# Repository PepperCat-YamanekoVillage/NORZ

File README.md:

# NORZ

NORZ is a project to create a Z80-compatible CPU using only NOR gates.

</br>

The project is progressing according to the following roadmap:
- [x] Draft the CPU design based on the Z80 specifications
- [x] Write the Verilog code
- [x] Debug the Verilog code
- [x] Implement the design on boards
- [x] Make a test board
- [x] Test the test board
- [ ] Debug the boards

</br>

### My blogs (ja)

[Gates consisting of NOR](https://yamanekovillage.com/articles/norz_1/)

[Modules consisting of NOR](https://yamanekovillage.com/articles/norz_2/)

[NORZ(Z80)\'s architecture](https://yamanekovillage.com/articles/norz_3/)

[NORZ on Verilog](https://yamanekovillage.com/articles/norz_4/)

[Debuging Verilog codes](https://yamanekovillage.com/articles/norz_5/)

[Design PCBs](https://yamanekovillage.com/articles/norz_6/)

[Make a test board (Failed)](https://yamanekovillage.com/articles/norz_7/)

</br>

## Confirmed instructions in Verilog

### 8-Bit Load Group
- [x] LD r,r’
- [x] LD r,n
- [x] LD r,(HL)
- [x] LD r,(IX+d)
- [x] LD r,(IY+d)
- [x] LD (HL),r
- [x] LD (IX+d),r
- [x] LD (IY+d),r
- [x] LD (HL),n
- [x] LD (IX+d),n
- [x] LD (IY+d),n
- [x] LD A,(BC)
- [x] LD A,(DE)
- [x] LD A,(nn)
- [x] LD (BC),A
- [x] LD (DE),A
- [x] LD (nn),A
- [x] LD A,I
- [x] LD A,R
- [x] LD I,A
- [x] LD R,A

### 16-Bit Load Group
- [x] LD dd,nn
- [x] LD IX,nn
- [x] LD IY,nn
- [x] LD HL,(nn)
- [x] LD dd,(nn)
- [x] LD IX,(nn)
- [x] LD IY,(nn)
- [x] LD (nn),HL
- [x] LD (nn),dd
- [x] LD (nn),IX
- [x] LD (nn),IY
- [x] LD SP,HL
- [x] LD SP,IX
- [x] LD SP,IY
- [x] PUSH qq
- [x] PUSH IX
- [x] PUSH IY
- [x] POP qq
- [x] POP IX
- [x] POP IY

### Exchange, Block Transfer, and Search Group
- [x] EX DE,HL
- [x] EX AF,AF
- [x] EXX
- [x] EX (SP),HL
- [x] EX (SP),IX
- [x] EX (SP),IY
- [x] LDI
- [x] LDIR
- [x] LDD
- [x] LDDR
- [x] CPI
- [x] CPIR
- [x] CPD
- [x] CPDR

### 8-Bit Arithmetic Group
- [x] ADD A,r
- [x] ADD A,n
- [x] ADD A,(HL)
- [x] ADD A,(IX+d)
- [x] ADD A,(IY+d)
- [x] ADC A,r
- [x] ADC A,n
- [x] ADC A,(HL)
- [x] ADC A,(IX+d)
- [x] ADC A,(IY+d)
- [x] SUB r
- [x] SUB n
- [x] SUB (HL)
- [x] SUB (IX+d)
- [x] SUB (IY+d)
- [x] SBC r
- [x] SBC n
- [x] SBC (HL)
- [x] SBC (IX+d)
- [x] SBC (IY+d)
- [x] AND r
- [x] AND n
- [x] AND (HL)
- [x] AND (IX+d)
- [x] AND (IY+d)
- [x] OR r
- [x] OR n
- [x] OR (HL)
- [x] OR (IX+d)
- [x] OR (IY+d)
- [x] XOR r
- [x] XOR n
- [x] XOR (HL)
- [x] XOR (IX+d)
- [x] XOR (IY+d)
- [x] CP r
- [x] CP n
- [x] CP (HL)
- [x] CP (IX+d)
- [x] CP (IY+d)
- [x] INC r
- [x] INC (HL)
- [x] INC (IX+d)
- [x] INC (IY+d)
- [x] DEC r
- [x] DEC (HL)
- [x] DEC (IX+d)
- [x] DEC (IY+d)

### General-Purpose Arithmetic and CPU Control Groups
- [x] DAA
- [x] CPL
- [x] NEG
- [x] CCF
- [x] SCF
- [x] NOP
- [x] HALT
- [x] DI
- [x] EI
- [x] IM 0
- [x] IM 1
- [x] IM 2

### 16-Bit Arithmetic Group
- [x] ADD HL,ss
- [x] ADC HL,ss
- [x] SBC HL,ss
- [x] ADD IX,pp
- [x] ADD IY,rr
- [x] INC ss
- [x] INC IX
- [x] INC IY
- [x] DEC ss
- [x] DEC IX
- [x] DEC IY

### Rotate and Shift Group
- [x] RLCA
- [x] RLA
- [x] RRCA
- [x] RRA
- [x] RLC r
- [x] RLC (HL)
- [x] RLC (IX+d)
- [x] RLC (IY+d)
- [x] RL r
- [x] RL (HL)
- [x] RL (IX+d)
- [x] RL (IY+d)
- [x] RRC r
- [x] RRC (HL)
- [x] RRC (IX+d)
- [x] RRC (IY+d)
- [x] RR r
- [x] RR (HL)
- [x] RR (IX+d)
- [x] RR (IY+d)
- [x] SLA r
- [x] SLA (HL)
- [x] SLA (IX+d)
- [x] SLA (IY+d)
- [x] SRA r
- [x] SRA (HL)
- [x] SRA (IX+d)
- [x] SRA (IY+d)
- [x] SRL r
- [x] SRL (HL)
- [x] SRL (IX+d)
- [x] SRL (IY+d)
- [x] RLD
- [x] RRD

### Bit Set, Reset, and Test Group
- [x] BIT b,r
- [x] BIT b,(HL)
- [x] BIT b,(IX+d)
- [x] BIT b,(IY+d)
- [x] SET b,r
- [x] SET b,(HL)
- [x] SET b,(IX+d)
- [x] SET b,(IY+d)
- [x] RES b,r
- [x] RES b,(HL)
- [x] RES b,(IX+d)
- [x] RES b,(IY+d)

### Jump Group
- [x] JP nn
- [x] JP cc,nn
- [x] JR e
- [x] JR C,e
- [x] JR NC,e
- [x] JR Z,e
- [x] JR NZ,e
- [x] JP (HL)
- [x] JP (IX)
- [x] JP (IY)
- [x] DJNZ e

### Call and Return Group
- [x] CALL nn
- [x] CALL cc,nn
- [x] RET
- [x] RET cc
- [x] RETI
- [x] RETN
- [x] RST p

### Input and Output Group
- [x] IN A,(n)
- [x] IN r,(C)
- [x] INI
- [x] INIR
- [x] IND
- [x] INDR
- [x] OUT (n),A
- [x] OUT (C),r
- [x] OUTI
- [x] OTIR
- [x] OUTD
- [x] OTDR

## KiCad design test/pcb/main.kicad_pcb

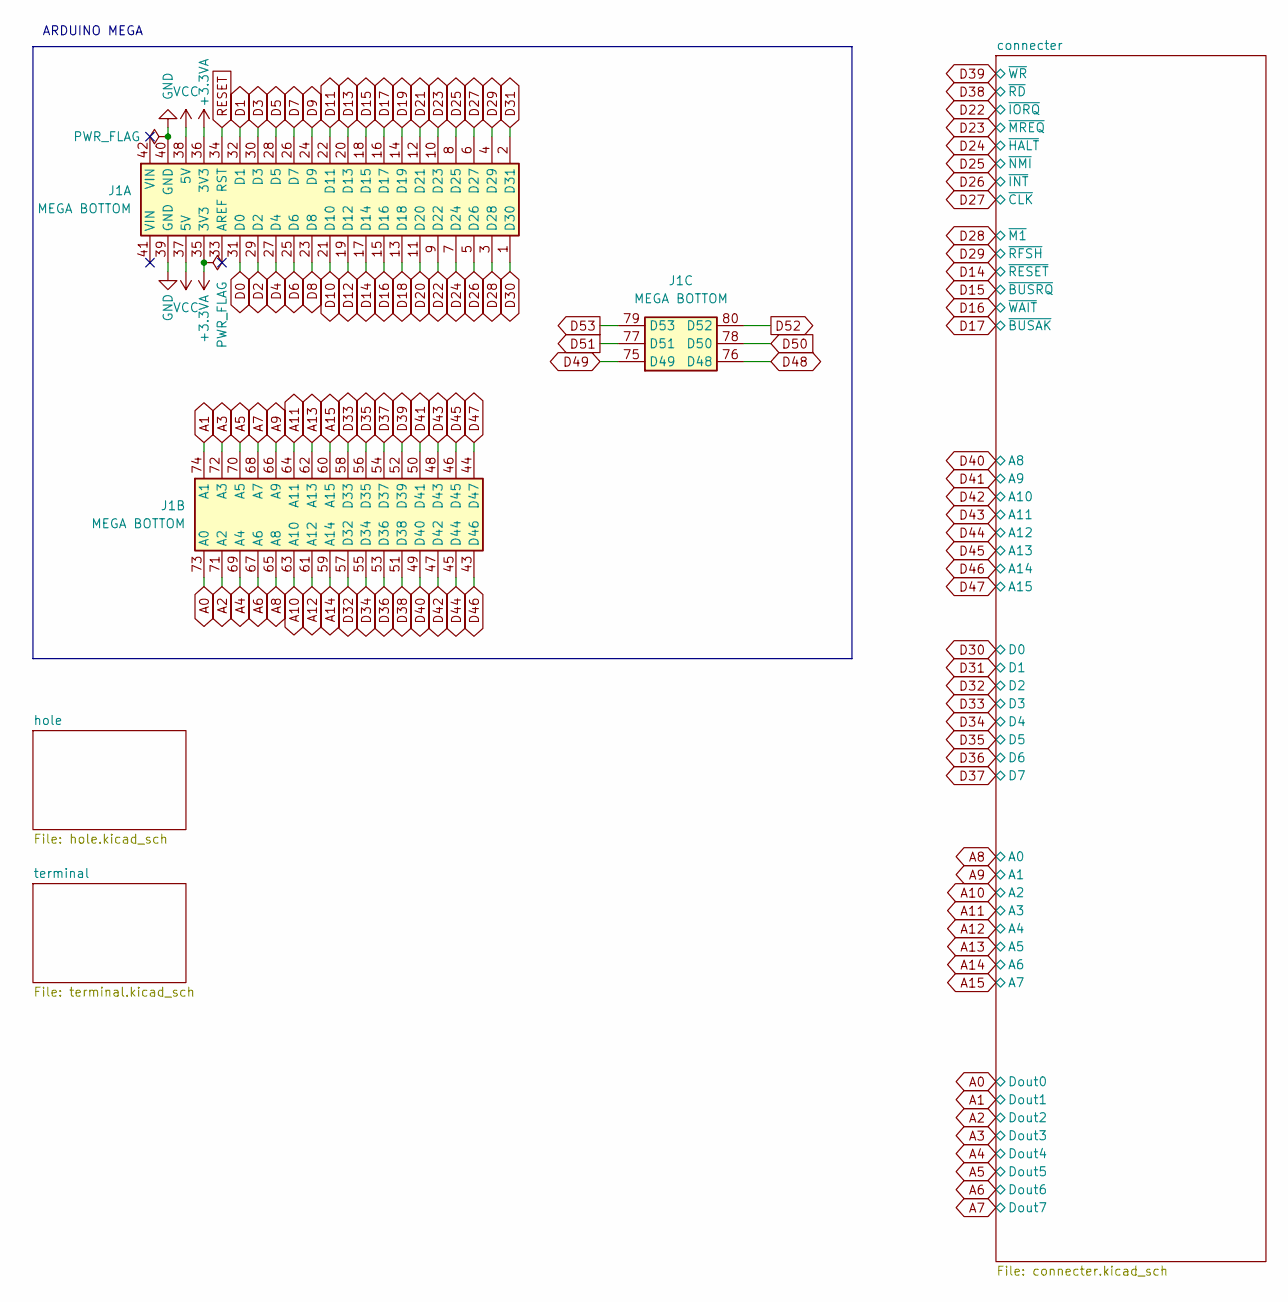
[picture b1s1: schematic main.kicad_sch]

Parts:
J1: MEGA BOTTOM; MEGA2560_PRO_MINI

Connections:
+3.3VA: J1.35 (3V3), J1.36 (3V3)
A0: J1.73 (A0); also elsewhere on the board
A1: J1.74 (A1); also elsewhere on the board
A2: J1.71 (A2); also elsewhere on the board
A3: J1.72 (A3); also elsewhere on the board
A4: J1.69 (A4); also elsewhere on the board
A5: J1.70 (A5); also elsewhere on the board
A6: J1.67 (A6); also elsewhere on the board
A7: J1.68 (A7); also elsewhere on the board
A8: J1.65 (A8); also elsewhere on the board
A9: J1.66 (A9); also elsewhere on the board
A10: J1.63 (A10); also elsewhere on the board
A11: J1.64 (A11); also elsewhere on the board
A12: J1.61 (A12); also elsewhere on the board
A13: J1.62 (A13); also elsewhere on the board
A14: J1.59 (A14); also elsewhere on the board
A15: J1.60 (A15); also elsewhere on the board
D0: J1.31 (D0)
D1: J1.32 (D1)
D2: J1.29 (D2)
D3: J1.30 (D3)
D4: J1.27 (D4)
D5: J1.28 (D5)
D6: J1.25 (D6)
D7: J1.26 (D7)
D8: J1.23 (D8)
D9: J1.24 (D9)
D10: J1.21 (D10)
D11: J1.22 (D11)
D12: J1.19 (D12)
D13: J1.20 (D13)
D14: J1.17 (D14); also elsewhere on the board
D15: J1.18 (D15); also elsewhere on the board
D16: J1.15 (D16); also elsewhere on the board
D17: J1.16 (D17); also elsewhere on the board
D18: J1.13 (D18)
D19: J1.14 (D19)
D20: J1.11 (D20)
D21: J1.12 (D21)
D22: J1.9 (D22); also elsewhere on the board
D23: J1.10 (D23); also elsewhere on the board
D24: J1.7 (D24); also elsewhere on the board
D25: J1.8 (D25); also elsewhere on the board
D26: J1.5 (D26); also elsewhere on the board
D27: J1.6 (D27); also elsewhere on the board
D28: J1.3 (D28); also elsewhere on the board
D29: J1.4 (D29); also elsewhere on the board
D30: J1.1 (D30); also elsewhere on the board
D31: J1.2 (D31); also elsewhere on the board
D32: J1.57 (D32); also elsewhere on the board
D33: J1.58 (D33); also elsewhere on the board
D34: J1.55 (D34); also elsewhere on the board
D35: J1.56 (D35); also elsewhere on the board
D36: J1.53 (D36); also elsewhere on the board
D37: J1.54 (D37); also elsewhere on the board
D38: J1.51 (D38); also elsewhere on the board
D39: J1.52 (D39); also elsewhere on the board
D40: J1.49 (D40); also elsewhere on the board
D41: J1.50 (D41); also elsewhere on the board
D42: J1.47 (D42); also elsewhere on the board
D43: J1.48 (D43); also elsewhere on the board
D44: J1.45 (D44); also elsewhere on the board
D45: J1.46 (D45); also elsewhere on the board
D46: J1.43 (D46); also elsewhere on the board
D47: J1.44 (D47); also elsewhere on the board
D48: J1.76 (D48)
D49: J1.75 (D49)
D50: J1.78 (D50)
D51: J1.77 (D51)
D52: J1.80 (D52)
D53: J1.79 (D53)
GND: J1.39 (GND), J1.40 (GND); also elsewhere on the board
RESET: J1.34 (RST)
VCC: J1.37 (5V), J1.38 (5V); also elsewhere on the board

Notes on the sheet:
ARDUINO MEGA

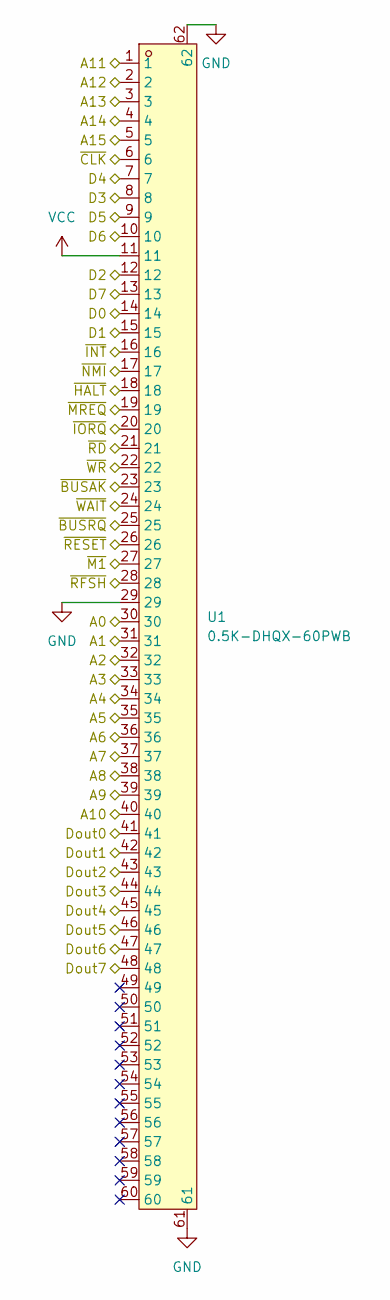
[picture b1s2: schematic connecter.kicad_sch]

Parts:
U1: 0.5K-DHQX-60PWB; FPC-SMD_60P-P0.50_HDGC_0.5K-DHQX-60PWB; LCSC Part C5292476

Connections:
A0: U1.41; also elsewhere on the board
A1: U1.42; also elsewhere on the board
A2: U1.43; also elsewhere on the board
A3: U1.44; also elsewhere on the board
A4: U1.45; also elsewhere on the board
A5: U1.46; also elsewhere on the board
A6: U1.47; also elsewhere on the board
A7: U1.48; also elsewhere on the board
A8: U1.30; also elsewhere on the board
A9: U1.31; also elsewhere on the board
A10: U1.32; also elsewhere on the board
A11: U1.33; also elsewhere on the board
A12: U1.34; also elsewhere on the board
A13: U1.35; also elsewhere on the board
A14: U1.36; also elsewhere on the board
A15: U1.37; also elsewhere on the board
D14: U1.26; also elsewhere on the board
D15: U1.25; also elsewhere on the board
D16: U1.24; also elsewhere on the board
D17: U1.23; also elsewhere on the board
D22: U1.20; also elsewhere on the board
D23: U1.19; also elsewhere on the board
D24: U1.18; also elsewhere on the board
D25: U1.17; also elsewhere on the board
D26: U1.16; also elsewhere on the board
D27: U1.6; also elsewhere on the board
D28: U1.27; also elsewhere on the board
D29: U1.28; also elsewhere on the board
D30: U1.14; also elsewhere on the board
D31: U1.15; also elsewhere on the board
D32: U1.12; also elsewhere on the board
D33: U1.8; also elsewhere on the board
D34: U1.7; also elsewhere on the board
D35: U1.9; also elsewhere on the board
D36: U1.10; also elsewhere on the board
D37: U1.13; also elsewhere on the board
D38: U1.21; also elsewhere on the board
D39: U1.22; also elsewhere on the board
D40: U1.38; also elsewhere on the board
D41: U1.39; also elsewhere on the board
D42: U1.40; also elsewhere on the board
D43: U1.1; also elsewhere on the board
D44: U1.2; also elsewhere on the board
D45: U1.3; also elsewhere on the board
D46: U1.4; also elsewhere on the board
D47: U1.5; also elsewhere on the board
GND: U1.29, U1.61, U1.62; also elsewhere on the board
VCC: U1.11; also elsewhere on the board

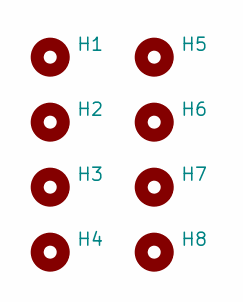
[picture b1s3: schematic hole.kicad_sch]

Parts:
H1, H2, H3, H4: MountingHole_3.2mm_M3_ISO7380; LCSC XXX
H5, H6, H7, H8: toolinghole; LCSC XXX

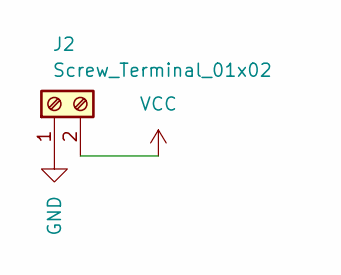
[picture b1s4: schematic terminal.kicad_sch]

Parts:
J2: Screw_Terminal_01x02; TerminalBlock_bornier-2_P5.08mm; LCSC XXX

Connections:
GND: J2.1; also elsewhere on the board
VCC: J2.2; also elsewhere on the board

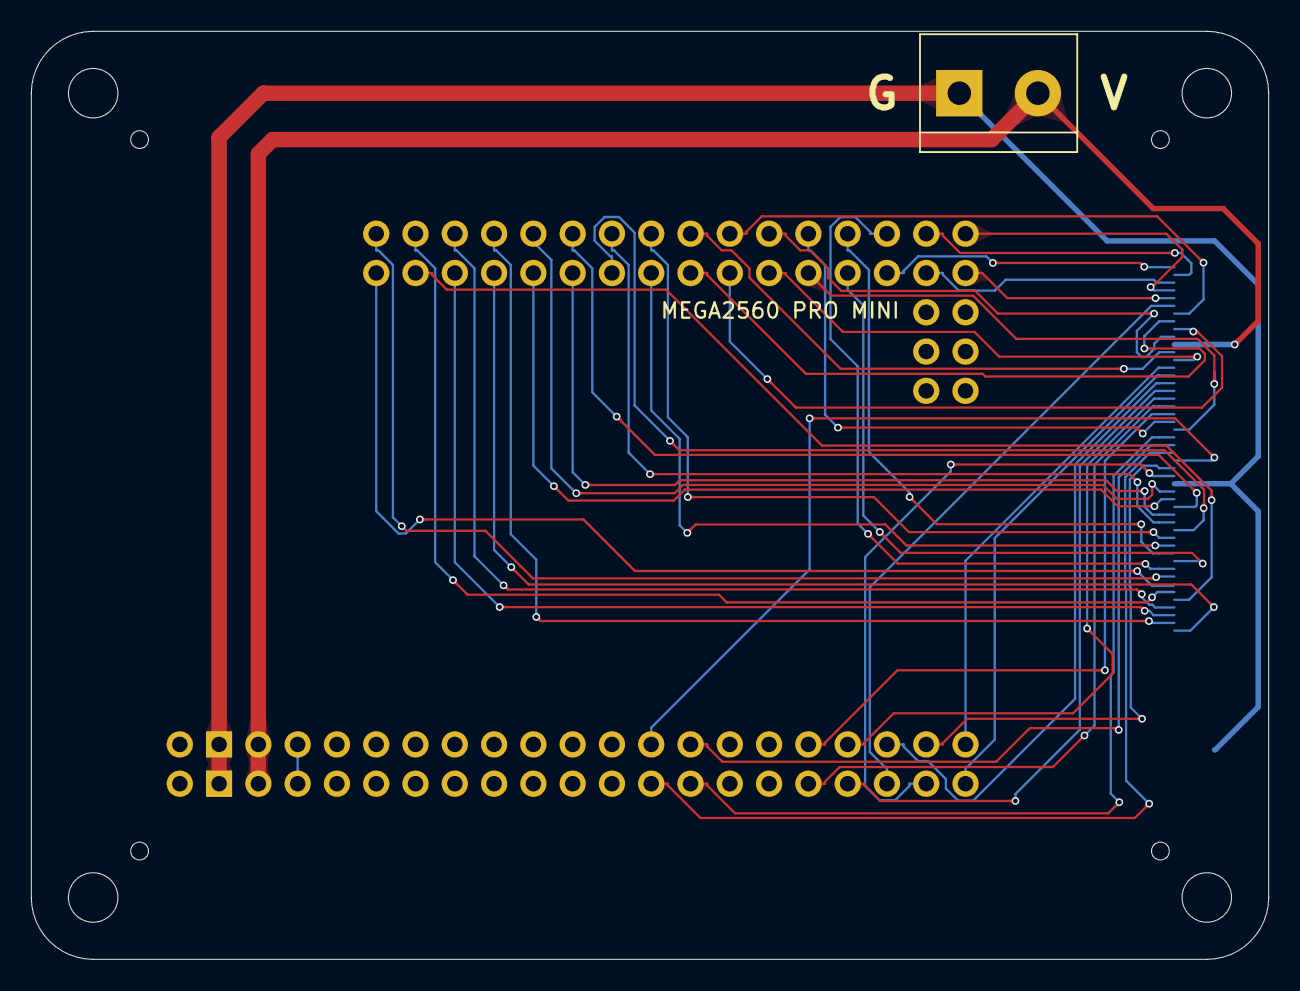
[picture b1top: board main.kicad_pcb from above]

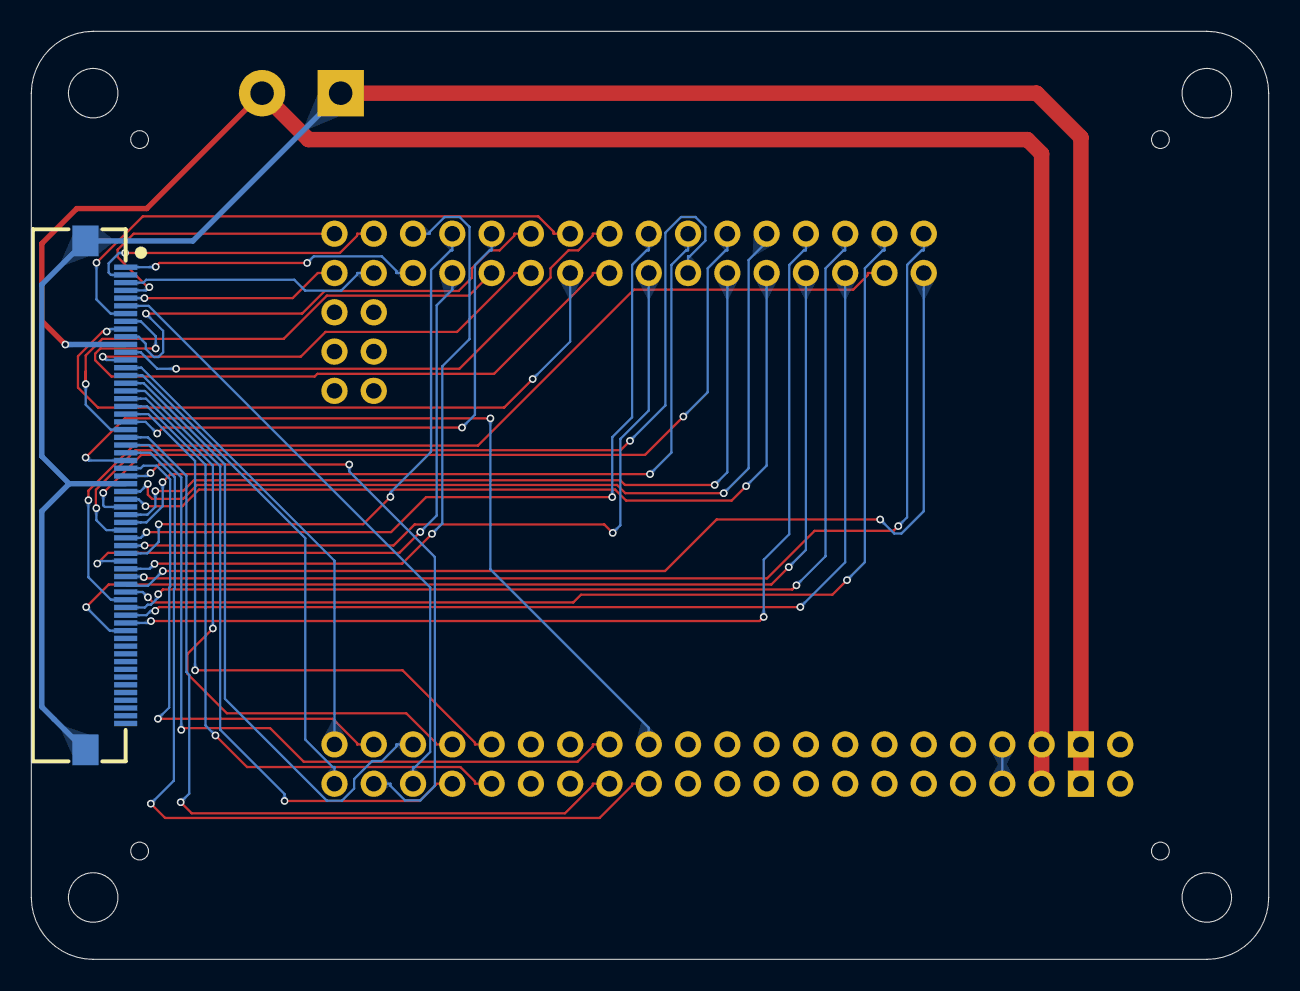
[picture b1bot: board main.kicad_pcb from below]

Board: 2 copper layers, 80.0 x 60.0 mm, 11 parts (2 on the bottom side), 49 nets.

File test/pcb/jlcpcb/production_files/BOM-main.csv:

Comment,Designator,Footprint,LCSC,Quantity
0.5K-DHQX-60PWB,U1,FPC-SMD_60P-P0.50_HDGC_0.5K-DHQX-60PWB,C5292476,1
Screw_Terminal_01x02,J2,TerminalBlock_bornier-2_P5.08mm,,1
MEGA BOTTOM,J1,MEGA2560_PRO_MINI,,1

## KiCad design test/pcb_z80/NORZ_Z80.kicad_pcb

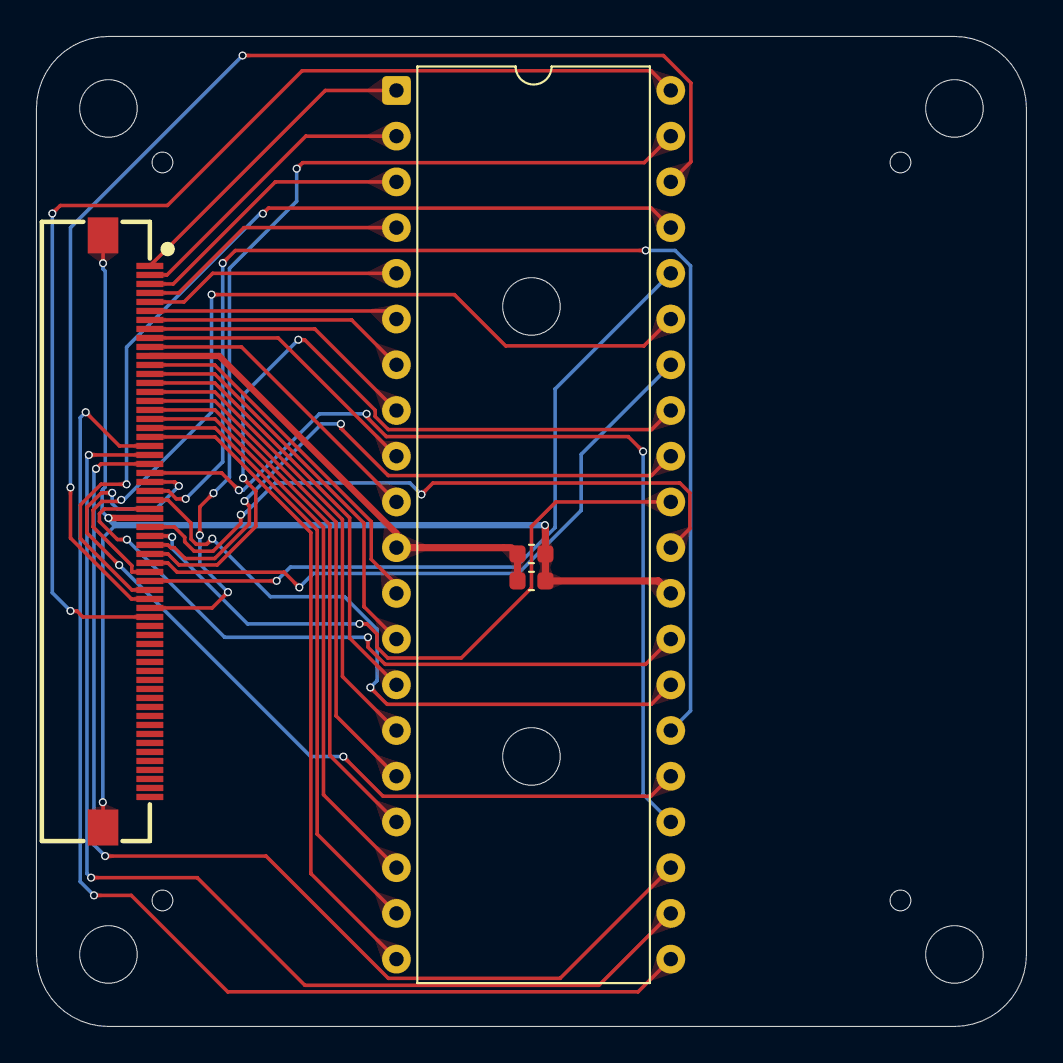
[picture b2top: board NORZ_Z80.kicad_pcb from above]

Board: 2 copper layers, 55.0 x 55.0 mm, 14 parts (0 on the bottom side), 40 nets.

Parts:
C1: 100nF; C_0603_1608Metric
C2: 22nF; C_0603_1608Metric
H1, H2, H3, H4, H9, H10: MountingHole_3.2mm_M3_ISO7380
H5, H6, H7, H8: toolinghole
U1: 0.5K-DHQX-60PWB; FPC-SMD_60P-P0.50_HDGC_0.5K-DHQX-60PWB
U2: Z84C00xxP; DIP-40_W15.24mm

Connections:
+5V: C1.1, C2.1, U1.11, U2.11 (V_{CC})
/connecter/A0: U1.30, U2.30 (A_{0})
/connecter/A1: U1.31, U2.31 (A_{1})
/connecter/A2: U1.32, U2.32 (A_{2})
/connecter/A3: U1.33, U2.33 (A_{3})
/connecter/A4: U1.34, U2.34 (A_{4})
/connecter/A5: U1.35, U2.35 (A_{5})
/connecter/A6: U1.36, U2.36 (A_{6})
/connecter/A7: U1.37, U2.37 (A_{7})
/connecter/A8: U1.38, U2.38 (A_{8})
/connecter/A9: U1.39, U2.39 (A_{9})
/connecter/A10: U1.40, U2.40 (A_{10})
/connecter/A11: U1.1, U2.1 (A_{11})
/connecter/A12: U1.2, U2.2 (A_{12})
/connecter/A13: U1.3, U2.3 (A_{13})
/connecter/A14: U1.4, U2.4 (A_{14})
/connecter/A15: U1.5, U2.5 (A_{15})
/connecter/D0: U1.14, U2.14 (D_{0})
/connecter/D1: U1.15, U2.15 (D_{1})
/connecter/D2: U1.12, U2.12 (D_{2})
/connecter/D3: U1.8, U2.8 (D_{3})
/connecter/D4: U1.7, U2.7 (D_{4})
/connecter/D5: U1.9, U2.9 (D_{5})
/connecter/D6: U1.10, U2.10 (D_{6})
/connecter/D7: U1.13, U2.13 (D_{7})
/connecter/~BUSAK: U1.23, U2.23 (~BUSACK)
/connecter/~BUSRQ: U1.25, U2.25 (~BUSREQ)
/connecter/~CLK: U1.6, U2.6 (CLK)
/connecter/~HALT: U1.18, U2.18 (~HALT)
/connecter/~INT: U1.16, U2.16 (~INT)
/connecter/~IORQ: U1.20, U2.20 (~IORQ)
/connecter/~M1: U1.27, U2.27 (~M1)
/connecter/~MREQ: U1.19, U2.19 (~MREQ)
/connecter/~NMI: U1.17, U2.17 (~NMI)
/connecter/~RD: U1.21, U2.21 (~RD)
/connecter/~RESET: U1.26, U2.26 (~RESET)
/connecter/~RFSH: U1.28, U2.28 (~RFSH)
/connecter/~WAIT: U1.24, U2.24 (~WAIT)
/connecter/~WR: U1.22, U2.22 (~WR)
GND: C1.2, C2.2, U1.29, U1.61, U1.62, U2.29 (GND)

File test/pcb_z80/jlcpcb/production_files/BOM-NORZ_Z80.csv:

Comment,Designator,Footprint,LCSC,Quantity
0.5K-DHQX-60PWB,U1,FPC-SMD_60P-P0.50_HDGC_0.5K-DHQX-60PWB,C5292476,1
22nF,C2,C_0603_1608Metric,,1
100nF,C1,C_0603_1608Metric,,1
Z84C00xxP,U2,DIP-40_W15.24mm,,1

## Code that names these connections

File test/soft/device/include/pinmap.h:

#ifndef PINMAP_H
#define PINMAP_H

#include <Arduino.h>

namespace pinmap {

static const uint8_t PIN_IORQ = 22;
static const uint8_t PIN_MREQ = 23;
static const uint8_t PIN_HALT = 24;
static const uint8_t PIN_NMI = 25;
static const uint8_t PIN_INT = 26;
static const uint8_t PIN_CLK = 27;
static const uint8_t PIN_M1 = 28;
static const uint8_t PIN_RFSH = 29;

static const uint8_t DATA_PINS[8] = {
    30, 31, 32, 33, 34, 35, 36, 37
};

static const uint8_t DOUT_PINS[8] = {
    54, 55, 56, 57, 58, 59, 60, 61
};

static const uint8_t ADDR_PINS[16] = {
    62, 63, 64, 65, 66, 67, 68, 69,
    40, 41, 42, 43, 44, 45, 46, 47
};

static const uint8_t PIN_RD = 38;
static const uint8_t PIN_WR = 39;
static const uint8_t PIN_RESET = 14;
static const uint8_t PIN_BUSRQ = 15;
static const uint8_t PIN_WAIT = 16;
static const uint8_t PIN_BUSAK = 17;

}  // namespace pinmap

#endif  // PINMAP_H

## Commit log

2024-10-06 VER 1.0.0
2024-10-11 FIX Bugs and ADD test tools
2024-10-18 Verilog Debug Complete
2026-03-23 MV codes&testes ->verilog/
2026-03-23 ADD test_brd
2026-03-23 Restore test results
